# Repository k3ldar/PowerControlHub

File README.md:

# PowerControlHub  
PowerControlHub is an Arduino-based 12V power distribution and control system for marine and off-grid applications. It provides configurable fused relay switching, multi-protocol sensor telemetry, WiFi/BLE/MQTT connectivity, and a companion touchscreen control panel — all managed through a unified serial command protocol and EEPROM-persisted configuration.

> Current firmware version: **1.0.0.0** — see [`FirmwareVersion.h`](PowerControlHub/FirmwareVersion.h).

---

## Table of Contents

- [Overview](#overview)
- [Prototype PCBs](#prototype-pcbs)
- [Key Features](#key-features)
- [Architecture](#architecture)
- [Board Support](#board-support)
- [Installation](#installation)
- [Configuration](#configuration)
- [Usage](#usage)
- [Subsystem Reference](#subsystem-reference)
- [Limitations and Known Issues](#limitations-and-known-issues)
- [Documentation](#documentation)
- [License](#license)

## Overview

PowerControlHub is a single-unit firmware target running on an Arduino Uno R4 WiFi or ESP32 NodeMCU-32. The Nextion touchscreen display is driven directly by the PCH controller over a dedicated hardware serial port (`Serial2` for GPS; display connected via `NextionControl`).

The firmware entry point is `PowerControlHubApp`, which owns all subsystem instances and wires them together at startup. Host and debug communication uses a text-based framed serial protocol:

```
<CMD>:<key>=<value>;<key>=<value>\n
```

Commands are grouped by prefix (`F`, `C`, `R`, `H`, `W`, `S`, `M`, `N`, `E`, `T`) and are available over serial, USB, and — where applicable — the HTTP REST API. See [Docs/Commands.md](Docs/Commands.md) for the full reference.

---

## Prototype PCBs

Prototype PCBs for **PowerControlHub** were supported by [PCBWay](https://www.pcbway.com), enabling rapid iteration from design to real-world testing.

See the [PCB Sponsorship & Manufacturing](Docs/pcbway.md) page for photos, build details, and ongoing testing.

---
## Key Features

### Relay Control
- Up to **8 independently configurable relay channels**, pin-assigned at runtime via configuration.
- **Linked relays** — any relay can be configured to mirror the state of another.
- **Default-on state** — individual relays can be initialised to active at boot.
- **Pulse mode** — relay activates for a configurable duration (seconds) then turns off automatically.
- **Named relays** — short name (5 chars) and long name (20 chars) stored in EEPROM for display use.
- **Action types** — relays can be designated as `Default`, `Horn` (COLREGS sound signal output), or `NightRelay` (automatic day/night switching driven by the LDR sensor).
- **Relay status bitmask** broadcast via `MessageBus` on every state change.

### Sensor Pipeline

All sensors inherit from `BaseSensor` and are registered with `SensorController`. The `RemoteSensor` class provides an extensibility point for sensors on external devices that push readings via serial.

| Sensor | Class | Poll Interval | Notes |
|---|---|---|---|
| **DHT11** | `Dht11SensorHandler` | 2 500 ms | Temperature (°C) and relative humidity (%). Raises `TemperatureSensorFailure` warning on read error; clears automatically on recovery. |
| **Light (LDR)** | `LightSensorHandler` | 30 000 ms | Rolling average over 10 readings. 3-reading debounce before day/night state change. Configurable ADC threshold (default 512). Drives a `NightRelay` automatically. |
| **Water Level** | `WaterSensorHandler` | Configurable | 15-reading rolling average. Active-pin corrosion-reduction control (power applied only during measurement). |
| **GPS** | `GpsSensorHandler` | Continuous | GY-GPS6MV2 (NMEA). Reports latitude, longitude, altitude, speed (km/h), course, cumulative distance. Provides UTC time for automatic RTC synchronisation. Raises `GpsFailure` warning if no valid fix for 30 seconds. |
| **System Diagnostics** | `SystemSensorHandler` | Configurable | Free heap memory, CPU usage percentage, WiFi/BT enabled state, SD log file size (bytes), system uptime (`d HH:MM:SS`), active warning count. |

Sensors expose data over Serial, WiFi REST, BLE, and MQTT. Custom local or remote sensors can be added with minimal boilerplate; see [Docs/Sensors.md](Docs/Sensors.md).

### Connectivity

#### WiFi
- Operates in **Access Point** or **Client** mode, selectable via `C12`.
- Implements **persistent HTTP connections** to reduce TCP handshake overhead on resource-constrained hardware.
- Supports up to **8 concurrent clients** (`MaxConcurrentClients`).
- Automatic reconnection with exponential backoff in Client mode.
- RSSI monitoring — raises `WeakWifiSignal` warning when signal falls below −70 dBm.
- Full REST API across 9 route groups:

| Route | Handler | Purpose |
|---|---|---|
| `/api/relay` | `RelayNetworkHandler` | Relay state read/write |
| `/api/sensor` | `SensorNetworkHandler` | Sensor telemetry |
| `/api/sound` | `SoundNetworkHandler` | COLREGS horn signals |
| `/api/system` | `SystemNetworkHandler` | System status, heartbeat, OTA |
| `/api/config` | `ConfigNetworkHandler` | Configuration read/write |
| `/api/warning` | `WarningNetworkHandler` | Warning bitmask access |
| `/api/timer` | `SchedulerNetworkHandler` | Scheduled event read |
| `/api/externalsensor` | `ExternalSensorNetworkHandler` | Remote sensor config |
| `/` | `WebIndexNetworkHandler` | Index page |

Uses a platform-abstraction interface (`IWifiRadio`) to isolate board-specific WiFi drivers from application logic.

#### Bluetooth BLE
- Available on boards with `BLUETOOTH_SUPPORT` defined.
- Exposes three GATT services via `BluetoothManager`:
  - `BluetoothSystemService` — system diagnostics characteristics.
  - `BluetoothSensorService` — sensor telemetry characteristics with notifications.
  - `BluetoothRelayService` — relay state read and write characteristics.
- Single-client model. Advertising restarts automatically after disconnect.
- No pairing or bonding. Device advertises as **"Power Control Hub"**.
- Uses `IBluetoothRadio` interface — higher-level code operates exclusively through the interface pointer, with runtime null-checks replacing compile-time guards.
- **Arduino Uno R4 WiFi constraint:** WiFi and BLE share the RF path on the ANNA-B112/ESP32-S3 modules; `BLUETOOTH_SUPPORT` and `WIFI_SUPPORT` are mutually exclusive on this board. Enforced by a compile-time `#error`. On ESP32, both can operate simultaneously.

#### MQTT
- Custom **MQTT 3.1.1** client implementation (`MQTTClient`) — no third-party MQTT library dependency.
- **Home Assistant auto-discovery** — all sensors and relays register as HA entities on connect.
- Configurable broker address (64 chars), credentials (32 chars each), device ID, discovery prefix, port (default 1883), and keepalive interval (default 60 s).
- Requires `WIFI_SUPPORT`. Guarded by `#if defined(WIFI_SUPPORT)` in `BoardConfig.h`.

### Warning System

A **32-bit bitmask** tracks up to 32 independent typed conditions within `WarningManager`.

- **Sensor failure aggregation**: any sensor warning (bits 21–31) automatically raises `SensorFailure` (bit 20). `SensorFailure` clears only when all sensor warnings are cleared.
- Warning state changes are broadcast on the `MessageBus` via `WarningChanged`.
- Full warning type reference: [Docs/Warnings.md](Docs/Warnings.md).

### Scheduler

Event-driven relay automation engine with EEPROM-persisted configuration.

- Up to **20 events** (6 on boards with ≤ 1 KB EEPROM) stored in `SchedulerSettings`.
- Each event specifies an independent **trigger**, **condition guard**, and **action**.

| Dimension | Supported Values |
|---|---|
| **Triggers** | `TimeOfDay`, `Sunrise`, `Sunset`, `Interval`, `DayOfWeek`, `Date` |
| **Conditions** | `TimeWindow`, `DayOfWeek`, `IsDark`, `IsDaylight`, `RelayIsOn`, `RelayIsOff` |
| **Actions** | `RelayOn`, `RelayOff`, `RelayToggle`, `RelayPulse`, `AllRelaysOn`, `AllRelaysOff`, `SetPinHigh`, `SetPinLow` |

Sunrise and sunset triggers are computed in real time from GPS coordinates by `SunCalculator`. The `IsDark` / `IsDaylight` conditions fall back to the LDR sensor when GPS is unavailable.

### Message Bus

`MessageBus` provides a **lightweight publish/subscribe event system** for internal component decoupling. No dynamic allocation occurs at publish time — subscriber lists use function-local statics.

Key events: `WarningChanged`, `RelayStatusChanged`, `TemperatureUpdated`, `HumidityUpdated`, `LightSensorUpdated`, `WaterLevelUpdated`, `GpsLocationUpdated`, `GpsAltitudeUpdated`, `GpsSpeedUpdated`, `WifiConnectionStateChanged`, `WifiSignalStrengthChanged`, `SystemMetricsUpdated`. Full reference: [Docs/MessageBus.md](Docs/MessageBus.md).

### Over-the-Air Updates (OTA)

- Available on **ESP32 + `WIFI_SUPPORT` + `OTA_AUTO_UPDATE`** only.
- Polls the GitHub Releases API (`k3ldar/PowerControlHub`) every **24 hours**.
- Downloads asset `PowerControlHub-esp32-v{major}.{minor}.{patch}.{build}.bin` with SHA-256 checksum verification.
- TLS connections use pinned root CA certificates (Sectigo E46 for `api.github.com`; ISRG Root X1 for `assets.githubusercontent.com`).
- **Auto-apply is disabled by default.** Enable via `F12:apply=1` or the `OtaFlagAutoApply` bit in `SystemHeader::reserved[0]`.
- OTA state (`idle`, `checking`, `available`, `downloading`, `rebooting`, `failed`, `uptodate`) is queryable at any time via `F13`.

### Diagnostics and Logging

- **SD card logging** via `SdCardLogger` / `MicroSdDriver`. Configurable SPI pins (`C4`). Raises `SpiPinConfigError`, `SdCardMissing`, `SdCardError`, or `SdCardLowSpace` warnings as appropriate.
- Optional **SD card config loader** (`CARD_CONFIG_LOADER`) — reads `config.txt` at boot to override EEPROM settings without reflashing.
- **DS1302 RTC** (`RtcDS1302Driver`) with configurable pins (`C18`). Automatically synchronised from GPS UTC time on each valid GPS fix.
- **CPU usage monitoring** via `SystemCpuMonitor`. Available over serial, WiFi, and MQTT.
- **Boot counter** and **crash counter** tracked in `SystemHeader` with magic number validation (`0x53464201`).
- **RGB LED warning indicator** (HW479) driven on configurable pins (`C8`).
- **PinGuard** — compile-time GPIO validation layer that rejects flash-reserved, input-only, and strapping pins at the point of assignment, returning `ACK:<cmd>=Invalid pin` before the value reaches EEPROM. Board-specific tables are selected automatically from the IDF toolchain macros — no manual configuration required. See [Docs/PinGuard.md](Docs/PinGuard.md).
- **Crash loop guard** — `crashCounter` in `SystemHeader` is incremented at the start of every boot and only reset after full initialisation succeeds. If the counter reaches `CrashCounterThreshold` (default 3), the firmware resets the config to safe defaults before any hardware initialisation runs, breaking a watchdog reset loop caused by invalid pin configuration.

### Nextion Display

- `NavigationController` manages an ordered list of active pages, rebuilt dynamically when the location type changes — no reboot required.
- Maritime-specific pages (buoys, cardinal markers, flags, VHF radio, COLREGS sound signals) are included in the page list only when `LocationType` is `Power`, `Sail`, `Fishing`, or `Yacht`.
- Pages included: Splash, Home, Relay, Relay Settings, Environment, System, Warning, Settings, About, Buoys, Cardinal Markers, Flags, Moon Phase, Sound (Fog / Maneuvering / Overtaking / Emergency / Other / Signals), VHF (Channels / Distress / Radio).

### Security

- **API key and HMAC key** fields (32 chars each) are reserved in the `Config` struct for future HTTP authentication.

---

## Architecture

### Repository Structure

```
PowerControlHub/    Firmware source (relays, sensors, WiFi, BLE, MQTT, OTA, SD, Nextion display)
Docs/            Reference documentation
TestData/        Serial command test scripts
```

### Subsystem Dependency Graph

```
PowerControlHubApp
├── MessageBus                  Pub/sub event bus (no dynamic allocation)
├── RelayController             Relay switching, linking, pulse, action types
├── SoundController             COLREGS signal sequencer -> horn relay
├── SensorController            Sensor pipeline (local + remote)
│   ├── Dht11SensorHandler
│   ├── LightSensorHandler
│   ├── WaterSensorHandler
│   ├── GpsSensorHandler
│   ├── SystemSensorHandler
│   └── RemoteSensor (xN)
├── ConfigController            EEPROM config lifecycle
├── WarningManager              32-bit bitmask, sensor failure aggregation
├── ScheduleController          Event engine: trigger -> condition -> action
├── WifiController              WiFi lifecycle, HTTP REST API
│   └── WifiServer              Connection state machine, request routing
├── BluetoothController         BLE lifecycle (BLUETOOTH_SUPPORT)
│   └── BluetoothManager
│       ├── BluetoothSystemService
│       ├── BluetoothSensorService
│       └── BluetoothRelayService
├── MQTTController              MQTT 3.1.1 client, HA auto-discovery (MQTT_SUPPORT)
├── SdCardLogger                SD card log writer (SD_CARD_SUPPORT)
├── RtcDS1302Driver             DS1302 real-time clock
├── OtaManager                  GitHub OTA (OTA_AUTO_UPDATE + ESP32 + WIFI_SUPPORT)
├── BroadcastManager            Centralised serial broadcast to computer/debug port
├── NavigationController        Nextion page navigation (NEXTION_DISPLAY_DEVICE)
└── SerialCommandManager        Framed serial command dispatch (USB/debug)
```

### Interface Abstraction Pattern

WiFi and Bluetooth subsystems are each accessed through a platform-agnostic interface (`IWifiRadio`, `IBluetoothRadio`). Board-specific drivers (`R4WifiRadio`, `Esp32WifiRadio`, `BluetoothController`) are constructed only inside `PowerControlHubApp` under the appropriate `#if defined(...)` guard. All higher-level code operates through interface pointers with runtime null-checks, minimising preprocessor usage and enabling straightforward test doubles.

### Configuration Persistence

The `Config` struct is a versioned, packed POD serialised to EEPROM. The current layout version is **6** (`ConfigVersion6`). The `SystemHeader` (32 bytes) precedes the config payload and contains a magic number (`0x53464201`), boot count, crash counter, reset reason, OTA flags, and a 16-bit checksum. A config version mismatch triggers migration logic in `ConfigManager` and raises `DefaultConfigurationFuseBox`.

---

## Board Support

| Board | WiFi | BLE | MQTT | OTA | Notes |
|---|---|---|---|---|---|
| **Arduino Uno R4 WiFi** | Yes | Yes | Yes | No | WiFi and BLE are mutually exclusive (shared RF path) |
| **Arduino Uno R4 Minima** | No | No | No | No | Serial and sensor support only |
| **ESP32 NodeMCU-32** | Yes | Yes | Yes | Yes | Full feature support; WiFi and BLE simultaneous |

Board selection is controlled by a single `#define` in `Local.h` using the trailing-underscore convention. `BoardConfig.h` derives all capability flags, EEPROM limits, and enforces incompatible feature combinations at compile time.

---

## Installation

### Prerequisites

| Requirement | Details |
|---|---|
| **Arduino IDE** | 1.8.19 or Arduino IDE 2.x |
| **Git for Windows** | Standard installation |
| **Windows 10 / 11** | No special configuration required |

### Required Libraries (Arduino Library Manager)

| Library | Source |
|---|---|
| `SerialCommandManager` | Si Carter |
| `DHT sensor library` | Adafruit |
| `QMC5883LCompass` | Arduino Library Manager |
| `NextionControl` | Custom — copy `NextionControl/` folder to Arduino `libraries/` directory |

### Steps

1. Clone the repository:

   ```
   git clone https://github.com/k3ldar/PowerControlHub
   ```

2. Install all required libraries via the Arduino IDE Library Manager, and copy `NextionControl` manually.

3. Open `k3ldar/PowerControlHub.ino` in the Arduino IDE.

4. Edit `Local.h` to activate the correct board and feature flags (see [Configuration](#configuration)).

5. Select the target board and COM port, then upload.

Full setup walkthrough: [Docs/SETUP.md](Docs/SETUP.md).

---

## Configuration

All hardware-specific configuration is isolated in a single file: `PowerControlHub/Local.h`. No other file requires modification for a standard hardware setup.

### Board Selection

Exactly one board define must be active. Remove the trailing underscore to activate:

```cpp
#define ARDUINO_UNO_R4       // Arduino Uno R4 WiFi
#define ARDUINO_R4_MINIMA_   // Arduino Uno R4 Minima (inactive)
#define ESP32_NODE_32_       // ESP32 NodeMCU-32 (inactive)
```

### Feature Flags

| Define | Default | Approx. Flash | Description |
|---|---|---|---|
| `FUSE_BOX_CONTROLLER` | Active | — | Enables the full SFB subsystem stack |
| `WIFI_SUPPORT` | Active | — | WiFi controller and HTTP REST API |
| `MQTT_SUPPORT` | Active | ~40 KB | MQTT client and HA auto-discovery (requires `WIFI_SUPPORT`) |
| `BLUETOOTH_SUPPORT` | Inactive | ~144 KB | BLE services (mutually exclusive with WiFi on Uno R4) |
| `SD_CARD_SUPPORT` | Active | ~32 KB | SD card logger and SPI driver |
| `NEXTION_DISPLAY_DEVICE` | Active | ~52 KB | Nextion display page system |
| `OTA_AUTO_UPDATE` | Active | ~165 KB | GitHub OTA (ESP32 + WiFi only) |
| `LED_MANAGER` | Inactive | — | Arduino R4 WiFi LED matrix (experimental) |
| `CARD_CONFIG_LOADER` | Inactive | — | Load config overrides from SD `config.txt` at boot |

### Relay Count

```cpp
constexpr uint8_t ConfigRelayCount = 8;  // number of relay channels
```

Pins are assigned at runtime via the `R11` serial command and persisted to EEPROM. `0xFF` marks a pin as unassigned.

Full configuration reference: [Docs/Local.md](Docs/Local.md).

---

## Usage

### Serial / USB Commands (Quick Reference)

Commands follow the frame format: `<CMD>:<key>=<value>;<key>=<value>\n`

```
# Save config to EEPROM
C0

# Enable WiFi in client mode, set SSID and password
C11:v=1
C12:v=1
C13:YourSSID
C14:YourPassword
C0

# Switch relay 0 on / off
R3:i=0;v=1
R3:i=0;v=0

# Query all relay states
R2

# Read temperature and humidity
S0
S1

# Enable MQTT and set broker
M0:v=1
M1:192.168.1.100
C0

# Enable Home Assistant auto-discovery
M6:v=1

# Query OTA status (ESP32 only)
F13

# Check for firmware update
F12

# Apply firmware update immediately
F12:apply=1
```

Full command reference (all groups, all parameters): [Docs/Commands.md](Docs/Commands.md).

### HTTP REST API (WiFi)

```
# Relay control
POST /api/relay/R3?i=0&v=1

# Sensor data
GET /api/sensor/S0

# System status
GET /api/system/F2

# OTA status
GET /api/system/F13
```

---

## Subsystem Reference

| Document | Contents |
|---|---|
| [Docs/Commands.md](Docs/Commands.md) | Full serial and REST command reference (all groups F, C, R, H, W, S, M, N, E, T) |
| [Docs/Local.md](Docs/Local.md) | `Local.h` configuration reference: board selection, feature flags, pin layout |
| [Docs/PinGuard.md](Docs/PinGuard.md) | GPIO validation: board pin tables, blocked pin tiers, crash loop guard |
| [Docs/Sensors.md](Docs/Sensors.md) | Sensor classes, poll intervals, MQTT channels, warning behaviour, extensibility guide |
| [Docs/Warnings.md](Docs/Warnings.md) | 32-bit warning type reference, `WarningManager` API, propagation model |
| [Docs/Wifi.md](Docs/Wifi.md) | WiFi architecture: connection state machine, persistent connection model, handler pattern |
| [Docs/BluetoothBle.md](Docs/BluetoothBle.md) | BLE service/characteristic reference, connection model, adding new services |
| [Docs/ScheduleEvents.md](Docs/ScheduleEvents.md) | Scheduler data structures, trigger/condition/action types, EEPROM layout |
| [Docs/MessageBus.md](Docs/MessageBus.md) | Event reference, publish/subscribe API |
| [Docs/SETUP.md](Docs/SETUP.md) | Prerequisites, library installation, build instructions |
| [Docs/BOM.md](Docs/BOM.md) | Bill of materials: hardware, fasteners, connectors, 3D-printed parts |

---

## Limitations and Known Issues

- **Arduino Uno R4 WiFi**: WiFi and BLE cannot operate simultaneously due to the shared RF hardware path. This is enforced at compile time.
- **Arduino Uno R4 Minima**: No radio support. Serial, sensors, and Nextion display only.
- **OTA updates**: Restricted to ESP32 targets with WiFi in client mode and `OTA_AUTO_UPDATE` defined. Not available on Arduino Uno R4.
- **Scheduler capacity**: Limited to 6 events on boards with 1 KB or less of EEPROM.
- **LED matrix manager** (`LED_MANAGER`): Experimental on Arduino R4 WiFi; not recommended for production use.
- **SD card support**: Marked experimental in `Local.h`. SPI pin configuration must be correct or `SpiPinConfigError` is raised.
- **Single BLE client**: Only one BLE central can be connected at a time. No pairing or bonding is implemented.

---

## Documentation

| Getting Started | Configuration | Connectivity |
|:---|:---|:---|
| [Setup Guide](Docs/SETUP.md) | [Local.h Reference](Docs/Local.md) | [WiFi Architecture](Docs/Wifi.md) |
| [Bill of Materials](Docs/BOM.md) | [Scheduled Events](Docs/ScheduleEvents.md) | [Bluetooth BLE](Docs/BluetoothBle.md) |
| [Sensor Reference](Docs/Sensors.md) | [Warning System](Docs/Warnings.md) | [Message Bus](Docs/MessageBus.md) |
| [Command Reference](Docs/Commands.md) | [PinGuard & Crash Loop](Docs/PinGuard.md) | |

---

## License

PowerControlHub is released under the **GNU General Public License v3.0**.  
See [LICENSE](LICENSE) for the full licence text.

Copyright &copy; 2025 Simon Carter (`s1cart3r@gmail.com`)

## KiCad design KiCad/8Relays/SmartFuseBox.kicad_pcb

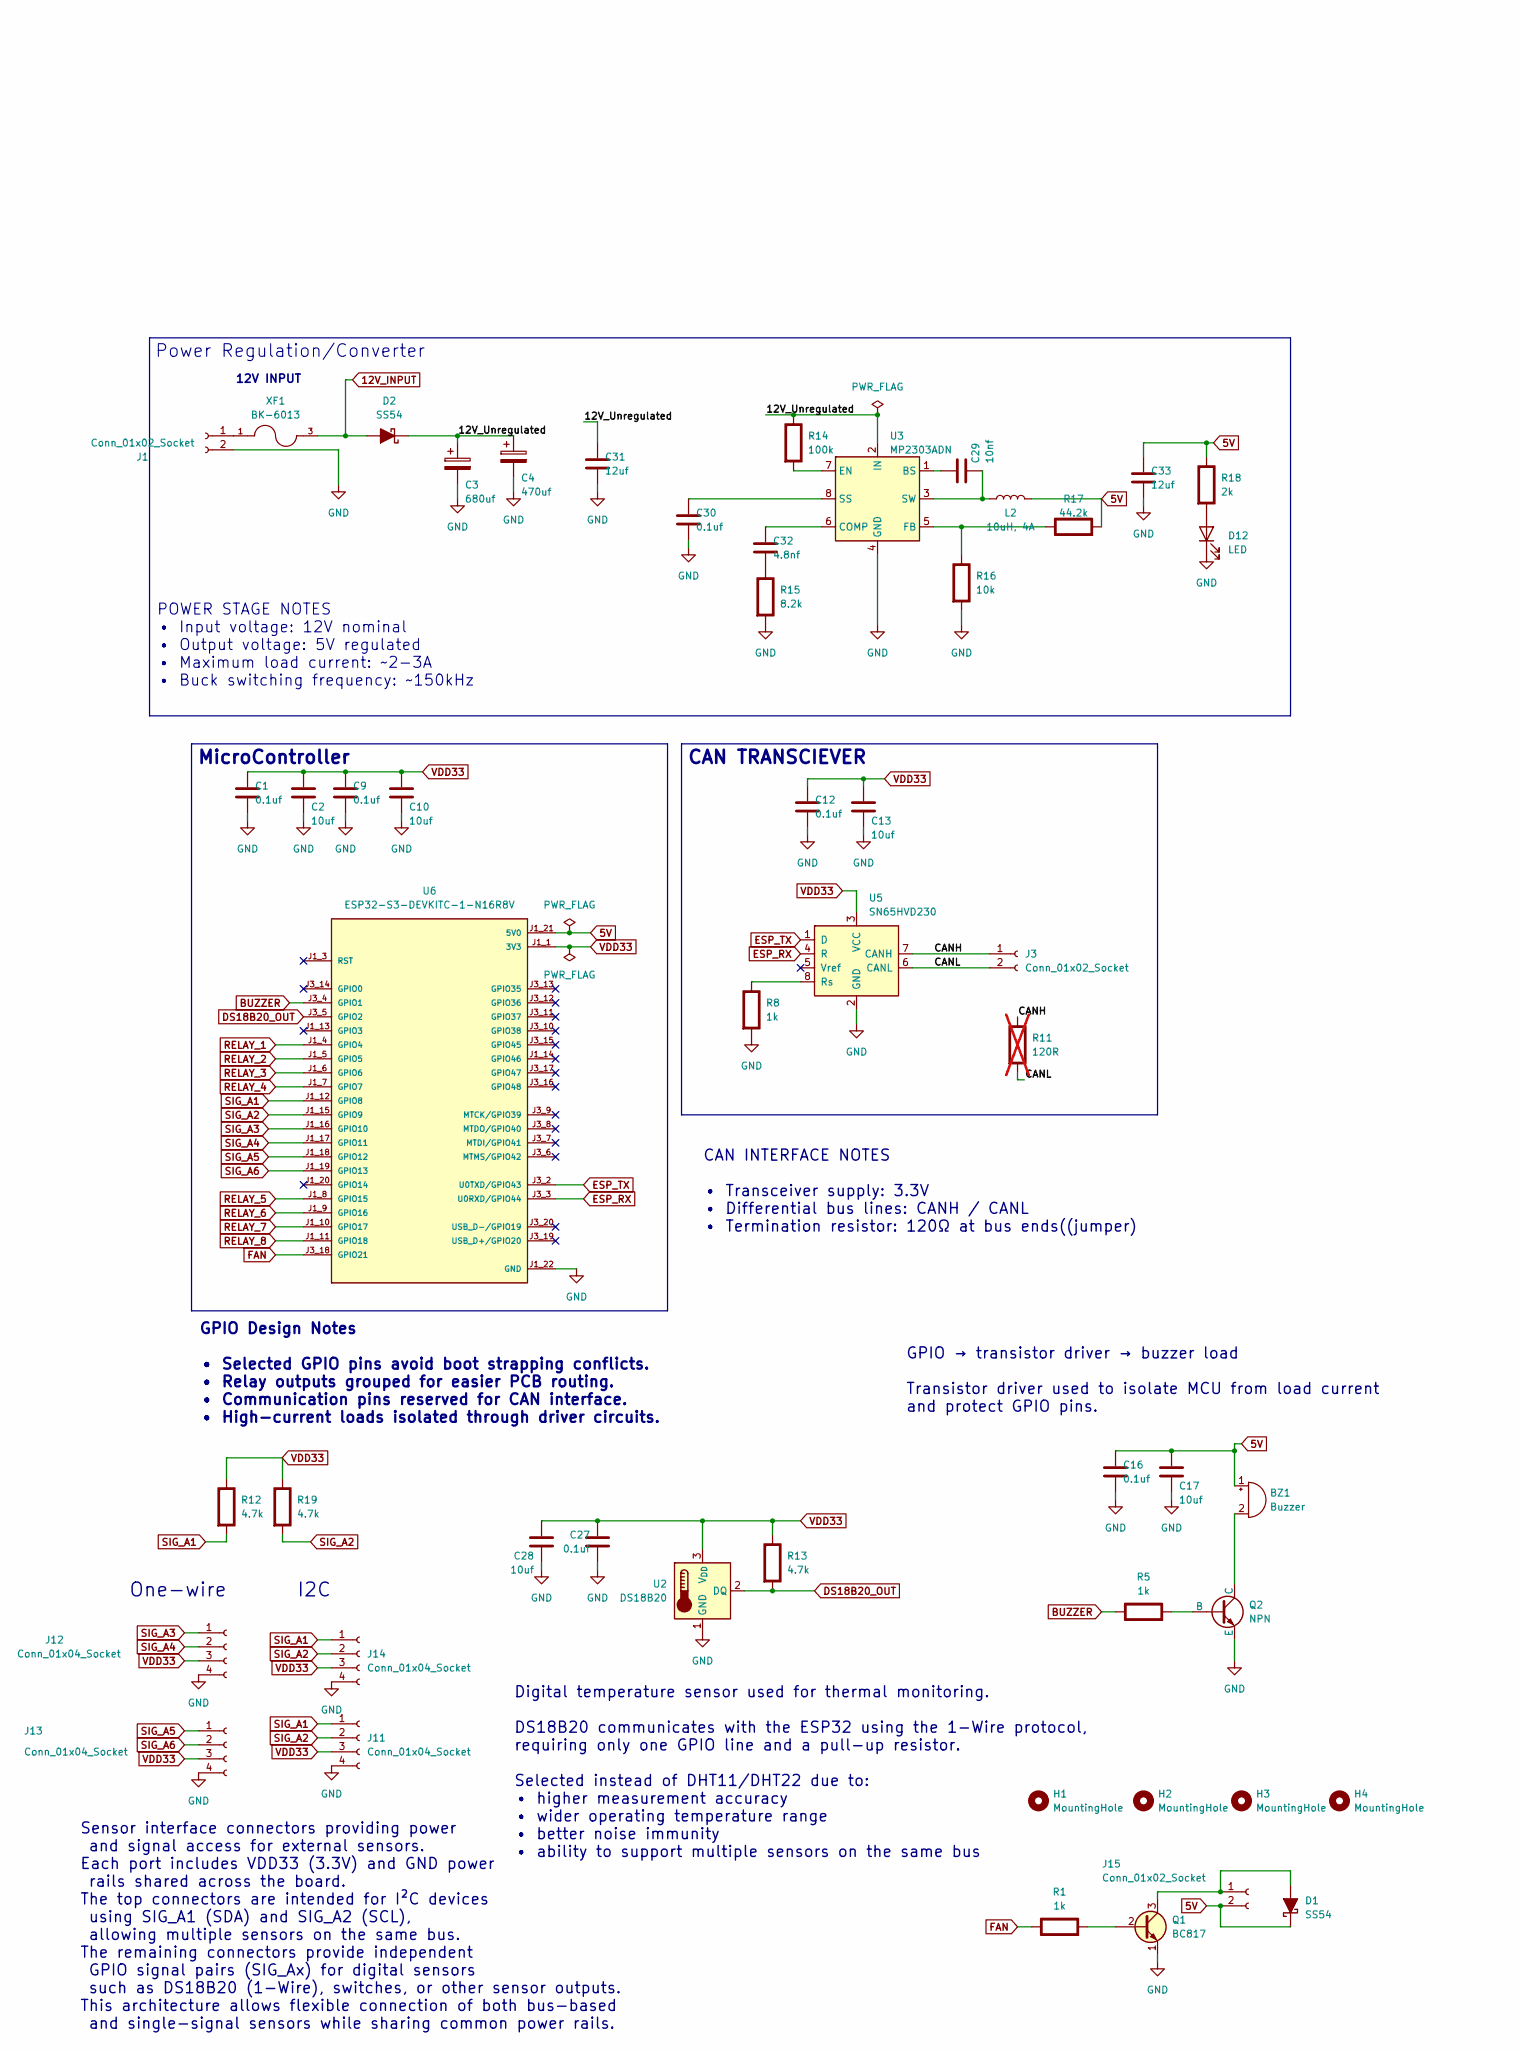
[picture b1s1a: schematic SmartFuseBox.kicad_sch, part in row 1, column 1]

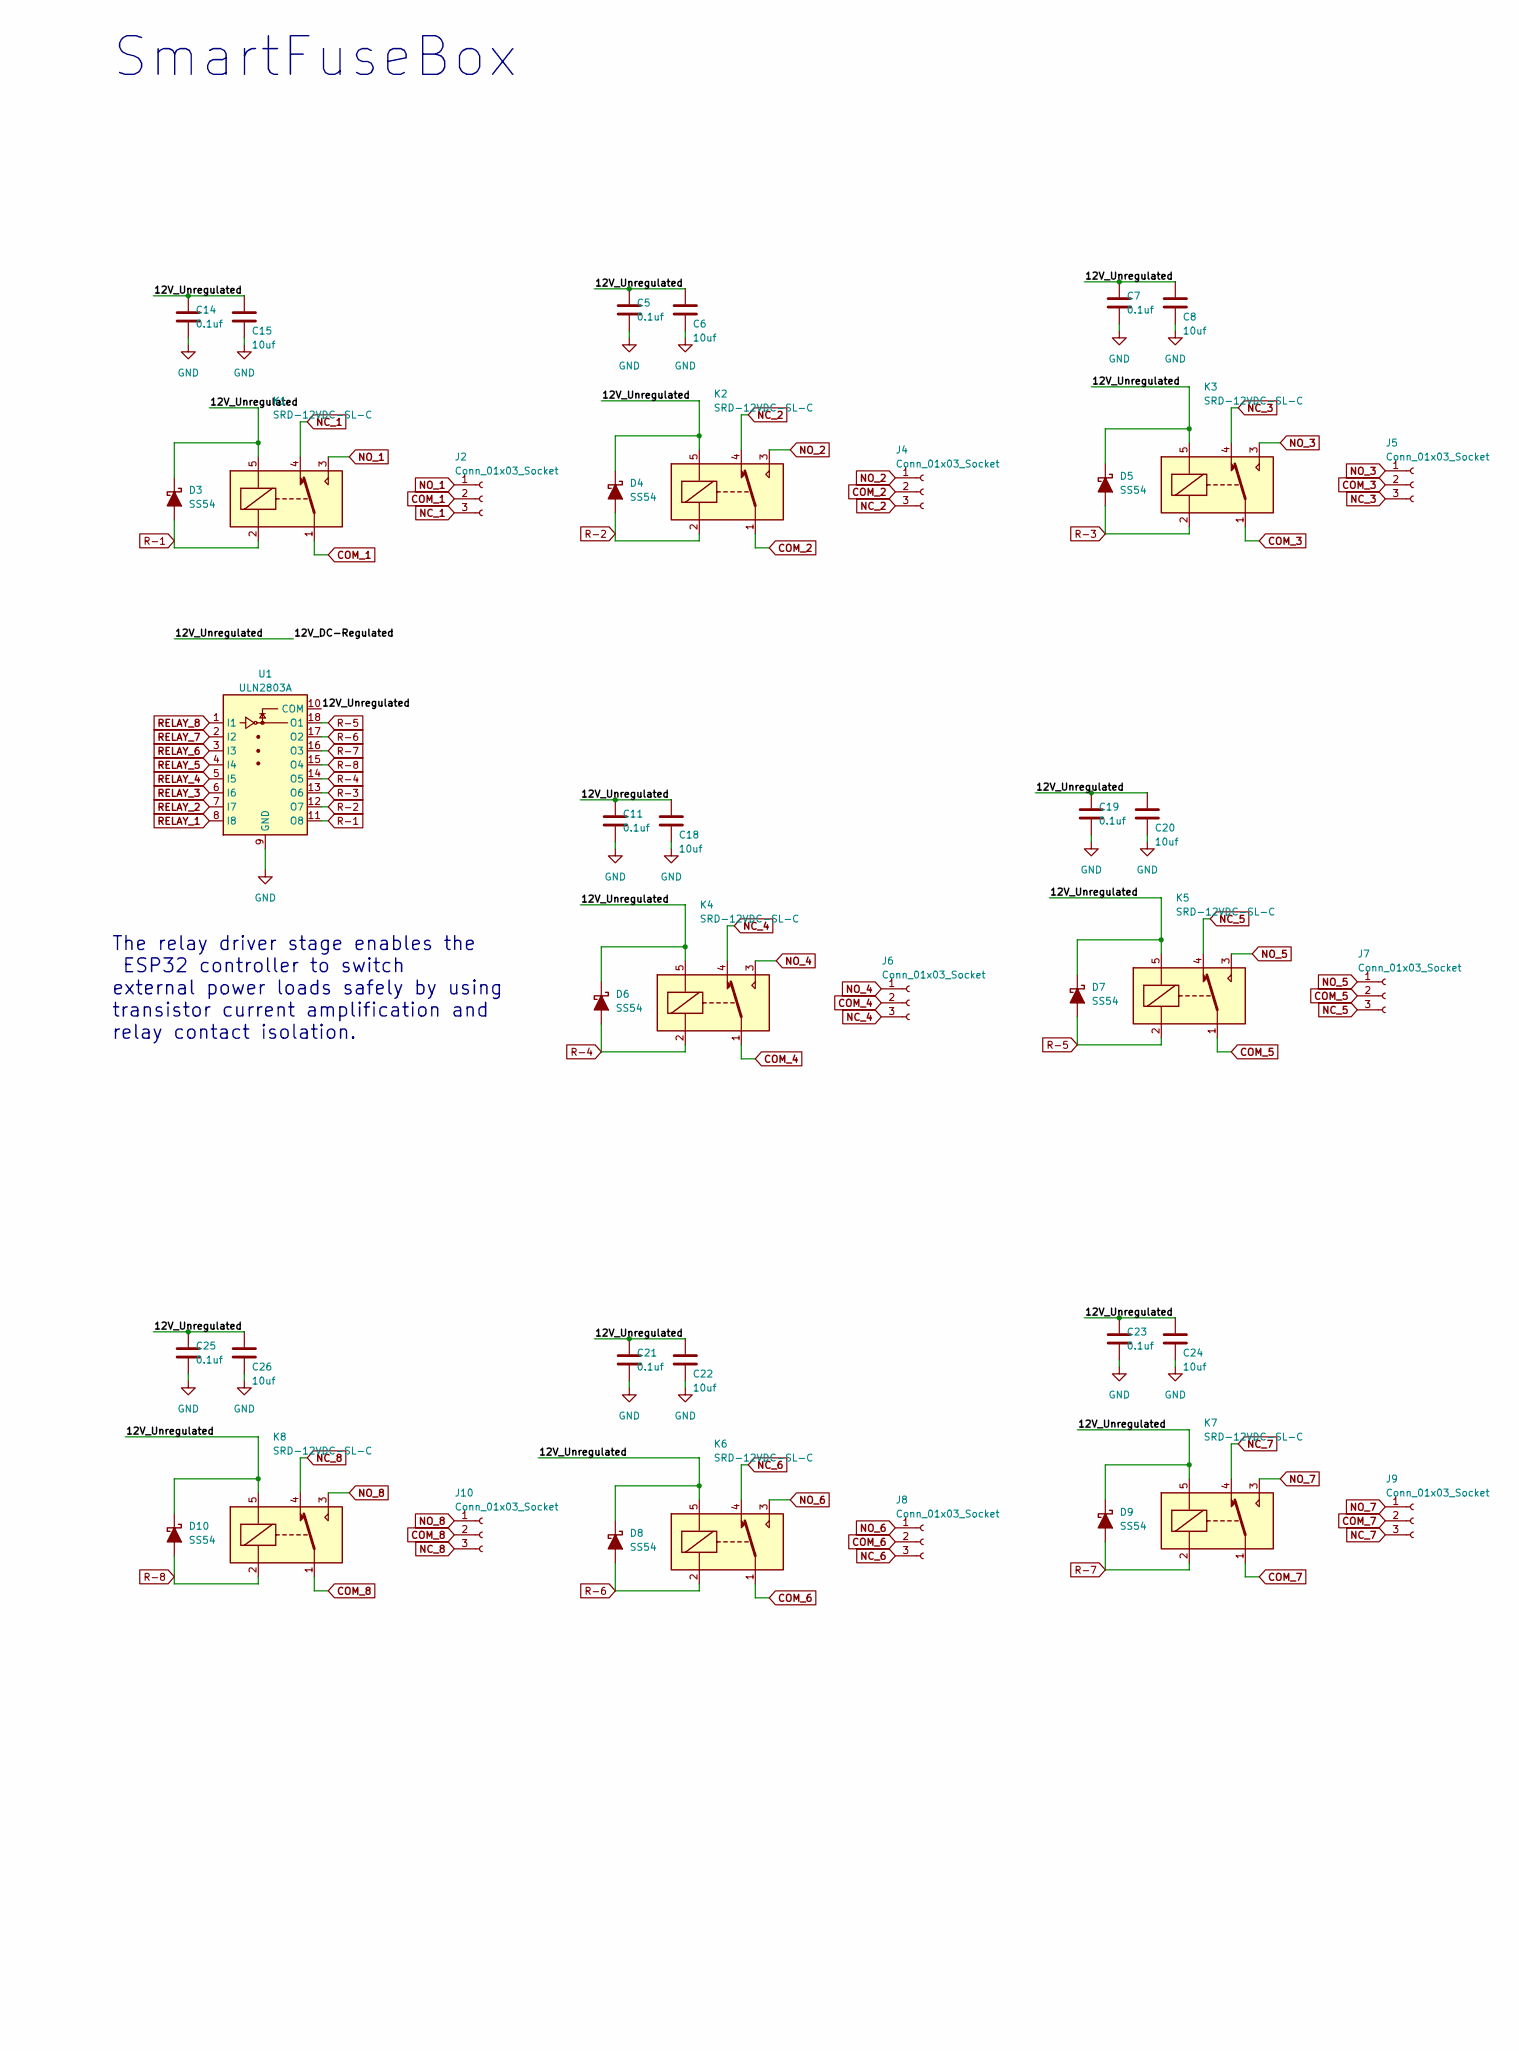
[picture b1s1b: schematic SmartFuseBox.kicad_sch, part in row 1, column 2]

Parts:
BZ1: Buzzer; Buzzer_12x9.5RM7.6
C1, C5, C7, C9, C11, C12, C14, C16, C19, C21, C23, C25, C27, C30: 0.1uf; C_0805_2012Metric_Pad1.18x1.45mm_HandSolder
C2, C6, C8, C10, C13, C15, C17, C18, C20, C22, C24, C26, C28: 10uf; C_0805_2012Metric_Pad1.18x1.45mm_HandSolder
C3: 680uf; CP_Elec_6.3x7.7
C4: 470uf; CP_Elec_10x10.5
C29: 10nf; C_0805_2012Metric_Pad1.18x1.45mm_HandSolder
C31, C33: 12uf; C_0805_2012Metric_Pad1.18x1.45mm_HandSolder
C32: 4.8nf; C_0805_2012Metric_Pad1.18x1.45mm_HandSolder
D1, D2, D3, D4, D5, D6, D7, D8, D9, D10: SS54; D_SMA
D12: LED; LED_0805_2012Metric_Pad1.15x1.40mm_HandSolder
H1, H2, H3, H4: MountingHole; MountingHole_3.2mm_M3
J1, J3: Conn_01x02_Socket; TerminalBlock_MaiXu_MX126-5.0-02P_1x02_P5.00mm
J2, J4, J5, J6, J7, J8, J9, J10: Conn_01x03_Socket; TerminalBlock_MaiXu_MX126-5.0-03P_1x03_P5.00mm
J11, J12, J13, J14: Conn_01x04_Socket; JST_PH_S4B-PH-K_1x04_P2.00mm_Horizontal
J15: Conn_01x02_Socket; JST_XH_S2B-XH-A-1_1x02_P2.50mm_Horizontal
K1, K2, K3, K4, K5, K6, K7, K8: SRD-12VDC-SL-C; Relay_SPDT_SANYOU_SRD_Series_Form_C
L2: 10uH, 4A; L_SOREDE_SNR.1050_10x10x5mm
Q1: BC817; SOT-23
Q2: NPN; SOT23-3_PO123
R1, R5, R8: 1k; R_0805_2012Metric_Pad1.20x1.40mm_HandSolder; Rating W
R11: 120R; R_0805_2012Metric_Pad1.20x1.40mm_HandSolder; Rating W; not fitted
R12, R13, R19: 4.7k; R_0805_2012Metric_Pad1.20x1.40mm_HandSolder; Rating W
R14: 100k; R_0805_2012Metric_Pad1.20x1.40mm_HandSolder; Rating W
R15: 8.2k; R_0805_2012Metric_Pad1.20x1.40mm_HandSolder; Rating W
R16: 10k; R_0805_2012Metric_Pad1.20x1.40mm_HandSolder; Rating W
R17: 44.2k; R_0805_2012Metric_Pad1.20x1.40mm_HandSolder; Rating W
R18: 2k; R_0805_2012Metric_Pad1.20x1.40mm_HandSolder; Rating W
U1: ULN2803A; SOIC-18W_7.5x11.6mm_P1.27mm
U2: DS18B20; TO-92_Inline
U3: MP2303ADN; SOIC-8-1EP_3.9x4.9mm_P1.27mm_EP2.62x3.51mm
U5: SN65HVD230; SOIC-8_3.9x4.9mm_P1.27mm
U6: ESP32-S3-DEVKITC-1-N16R8V; XCVR_ESP32-S3-DEVKITC-1-N16R8V; PARTREV 1.1
XF1: BK-6013; FUSE_BK-6013; PARTREV 02/07/14

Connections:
5V: BZ1.1 (+), C16.1, C17.1, C33.1, D1.1 (K), J15.2, L2.2, R17.2 (-), R18.1 (+), U6.J1_21 (5V0)
12V_INPUT: D2.2 (A), XF1.3, XF1.4
/12V_DC-Regulated: C3.1, C4.1, C5.1, C6.1, C7.1, C8.1, C11.1, C14.1, C15.1, C18.1, C19.1, C20.1, C21.1, C22.1, C23.1, C24.1, C25.1, C26.1, C31.1, D2.1 (K), D3.1 (K), D4.1 (K), D5.1 (K), D6.1 (K), D7.1 (K), D8.1 (K), D9.1 (K), D10.1 (K), K1.5, K2.5, K3.5, K4.5, K5.5, K6.5, K7.5, K8.5, R14.1 (+), U1.10 (COM), U3.2 (IN)
/CANH: J3.1, R11.1 (+), U5.7 (CANH)
/CANL: J3.2, R11.2 (-), U5.6 (CANL)
BUZZER: R5.1 (+), U6.J3_4 (GPIO1)
COM_1: J2.2, K1.1
COM_2: J4.2, K2.1
COM_3: J5.2, K3.1
COM_4: J6.2, K4.1
COM_5: J7.2, K5.1
COM_6: J8.2, K6.1
COM_7: J9.2, K7.1
COM_8: J10.2, K8.1
DS18B20_OUT: R13.2 (-), U2.2 (DQ), U6.J3_5 (GPIO2)
ESP_RX: U5.4 (R), U6.J3_3 (U0RXD/GPIO44)
ESP_TX: U5.1 (D), U6.J3_2 (U0TXD/GPIO43)
FAN: R1.1 (+), U6.J3_18 (GPIO21)
GND: C1.2, C2.2, C3.2, C4.2, C5.2, C6.2, C7.2, C8.2, C9.2, C10.2, C11.2, C12.2, C13.2, C14.2, C15.2, C16.2, C17.2, C18.2, C19.2, C20.2, C21.2, C22.2, C23.2, C24.2, C25.2, C26.2, C27.2, C28.2, C30.2, C31.2, C33.2, D12.1 (K), J1.2, J11.4, J12.4, J13.4, J14.4, Q1.1 (E), Q2.3 (E), R8.2 (-), R15.2 (-), R16.2 (-), U1.9 (GND), U2.1 (GND), U3.4 (GND), U5.2 (GND), U6.J1_22 (GND), U6.J3_1 (GND), U6.J3_21 (GND), U6.J3_22 (GND)
NC_1: J2.3, K1.4
NC_2: J4.3, K2.4
NC_3: J5.3, K3.4
NC_4: J6.3, K4.4
NC_5: J7.3, K5.4
NC_6: J8.3, K6.4
NC_7: J9.3, K7.4
NC_8: J10.3, K8.4
NO_1: J2.1, K1.3
NO_2: J4.1, K2.3
NO_3: J5.1, K3.3
NO_4: J6.1, K4.3
NO_5: J7.1, K5.3
NO_6: J8.1, K6.3
NO_7: J9.1, K7.3
NO_8: J10.1, K8.3
unnamed: BZ1.2 (-), Q2.1 (C)
unnamed: D1.2 (A), J15.1, Q1.3 (C)
unnamed: D12.2 (A), R18.2 (-)
unnamed: J1.1, XF1.1, XF1.2
unnamed: Q1.2 (B), R1.2 (-)
unnamed: Q2.2 (B), R5.2 (-)
unnamed: R8.1 (+), U5.8 (Rs)
unnamed: R14.2 (-), U3.7 (EN)
unnamed: C32.2, R15.1 (+)
unnamed: R16.1 (+), R17.1 (+), U3.5 (FB)
unnamed: C29.1, U3.1 (BS)
unnamed: C32.1, U3.6 (COMP)
unnamed: C30.1, U3.8 (SS)
unnamed: C29.2, L2.1, U3.3 (SW)
R-1: D3.2 (A), K1.2, U1.11 (O8)
R-2: D4.2 (A), K2.2, U1.12 (O7)
R-3: D5.2 (A), K3.2, U1.13 (O6)
R-4: D6.2 (A), K4.2, U1.14 (O5)
R-5: D7.2 (A), K5.2, U1.18 (O1)
R-6: D8.2 (A), K6.2, U1.17 (O2)
R-7: D9.2 (A), K7.2, U1.16 (O3)
R-8: D10.2 (A), K8.2, U1.15 (O4)
RELAY_1: U1.8 (I8), U6.J1_4 (GPIO4)
RELAY_2: U1.7 (I7), U6.J1_5 (GPIO5)
RELAY_3: U1.6 (I6), U6.J1_6 (GPIO6)
RELAY_4: U1.5 (I5), U6.J1_7 (GPIO7)
RELAY_5: U1.4 (I4), U6.J1_8 (GPIO15)
RELAY_6: U1.3 (I3), U6.J1_9 (GPIO16)
RELAY_7: U1.2 (I2), U6.J1_10 (GPIO17)
RELAY_8: U1.1 (I1), U6.J1_11 (GPIO18)
SIG_A1: J11.1, J14.1, R12.2 (-), U6.J1_12 (GPIO8)
SIG_A2: J11.2, J14.2, R19.2 (-), U6.J1_15 (GPIO9)
SIG_A3: J12.1, U6.J1_16 (GPIO10)
SIG_A4: J12.2, U6.J1_17 (GPIO11)
SIG_A5: J13.1, U6.J1_18 (GPIO12)
SIG_A6: J13.2, U6.J1_19 (GPIO13)
VDD33: C1.1, C2.1, C9.1, C10.1, C12.1, C13.1, C27.1, C28.1, J11.3, J12.3, J13.3, J14.3, R12.1 (+), R13.1 (+), R19.1 (+), U2.3 (V_{DD}), U5.3 (VCC), U6.J1_1 (3V3), U6.J1_2 (3V3)

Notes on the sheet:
Sensor interface connectors providing power and signal access for external sensors. Each port includes VDD33 (3.3V) and GND power rails shared across the board. The top connectors are intended for I²C devices using SIG_A1 (SDA) and SIG_A2 (SCL), allowing multiple sensors on the same bus. The remain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
The relay driver stage enables the ESP32 controller to switch external power loads safely by using transistor current amplification and relay contact isolation.
GPIO Design Notes • Selected GPIO pins avoid boot strapping conflicts. • Relay outputs grouped for easier PCB routing. • Communication pins reserved for CAN interface. • High-current loads isolated through driver circuits.
I2C
CAN INTERFACE NOTES • Transceiver supply: 3.3V • Differential bus lines: CANH / CANL • Termination resistor: 120Ω at bus ends((jumper)
${TITLE}
One-wire
12V INPUT
GPIO → transistor driver → buzzer load Transistor driver used to isolate MCU from load current and protect GPIO pins.
Digital temperature sensor used for thermal monitoring. DS18B20 communicates with the ESP32 using the 1-Wire protocol, requiring only one GPIO line and a pull-up resistor. Selected instead of DHT11/DHT22 due to: • higher measurement accuracy • wider operating temperature range • better noise immuni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
POWER STAGE NOTES • Input voltage: 12V nominal • Output voltage: 5V regulated • Maximum load current: ~2-3A • Buck switching frequency: ~150kHz
Power Regulation/Converter
MicroController
CAN TRANSCIEVER

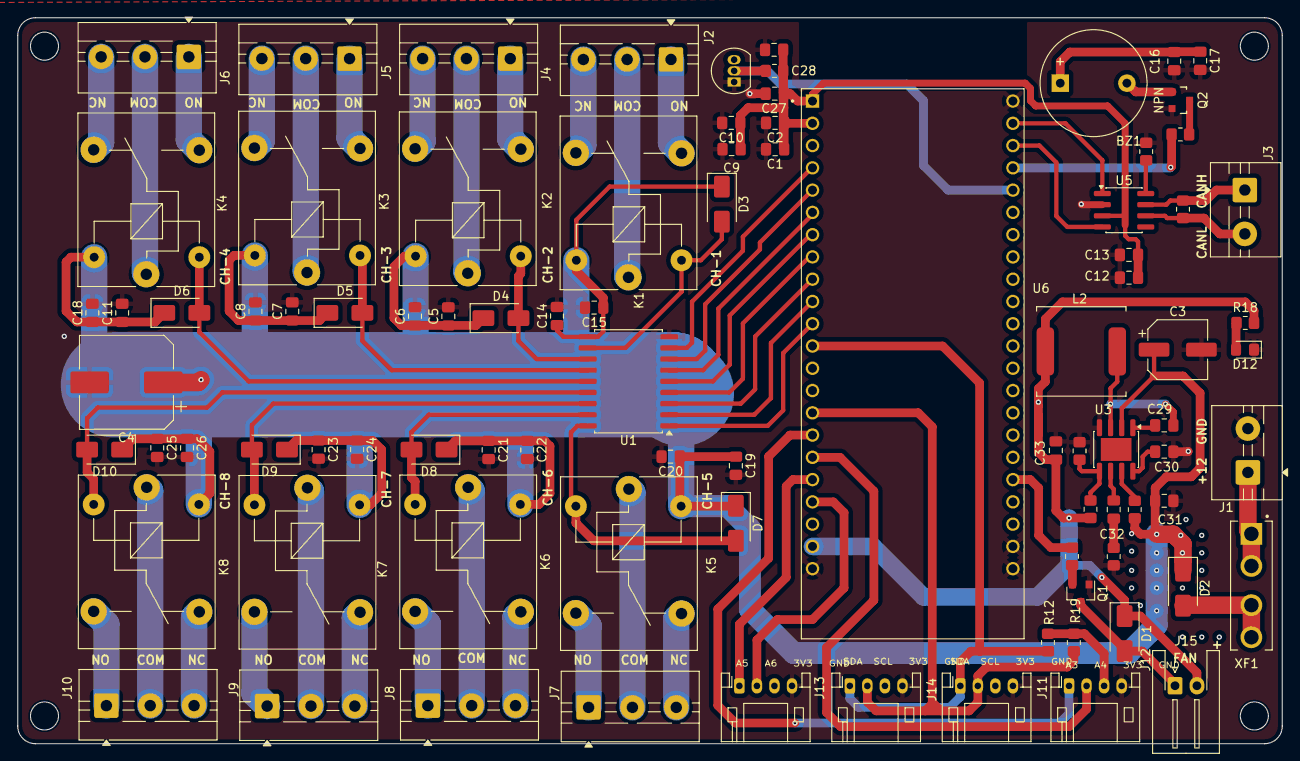
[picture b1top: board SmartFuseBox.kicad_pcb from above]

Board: 4 copper layers, 144.2 x 82.8 mm, 93 parts (0 on the bottom side), 72 nets.

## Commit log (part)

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2025-11-16 Auto name relay for sound commands Include BroadcastManager for multi serial comms
2025-11-16 Initial plan
2025-11-17 Sensor management part 1
2025-11-18 Send warning to control panel
2025-11-20 Initial sharing of code between projects using symbolic links
2025-11-20 Feature/shared code (#36)
    * Initial sharing of code between projects using symbolic links
    * Add board used in local
2025-11-20 Add documentation and error handling to UpdateSymLinks.bat
2025-11-20 Add fixes for sym link files along with documentation
2025-11-20 Add fixes for sym link files along with documentation (#42)
2025-11-21 Clean up SymLink creation and remove duplicate batch code
2025-11-21 Rename StaticElectrics to SmartFuseBox
2025-11-21 Rename StaticElectrics to SmartFuseBox (#43)
2025-11-22 Finalise shared code between projects
2025-11-23 Update warning page, extend for default configuration both sides.
    Fix memory issue on UnoR4
    Cpu Monitoring and new monitor page on nextion
2025-11-24 Update warning page, extend for default configuration both sides. (#45)
    Fix memory issue on UnoR4
    Cpu Monitoring and new monitor page on nextion
2025-11-25 Update global variables which are used within Nextion
2025-11-25 Update global variables which are used within Nextion (#46)
2025-11-25 Fix all global variable names for smoother display
2025-11-25 Implement about page
2025-11-27 Initial bt offering, still has issues before pushing
2025-11-28 Finished bluetooth integration
2025-11-28 add relay service
2025-11-28 Feature/bluetooth (#49)
    * Finished bluetooth integration
2025-11-29 Introduce standard logging
2025-11-29 Fix issue with BroadcastManager and add queue to shared
2025-11-30 Initial non blocking wifi server
2025-11-30 Implement with wifi controller
2025-12-01 Integrate wifi into smart fuse box, only has relay at present, the remainder will form part of other PRs
2025-12-01 Feature/wifi (#54)
    * Initial non blocking wifi server
    * Implement with wifi controller
    * Pre full integration test
    * Integrate wifi into smart fuse box, only has relay at present, the remainder will form part of other PRs
2025-12-01 rename sound manager to sound controller as part of middleware
2025-12-02 Complete sound network handler, refactored existing handler in the process
2025-12-02 Validate wifi strength
2025-12-02 Feature/wifi sound command handler (#67)
    * rename sound manager to sound controller as part of middleware
    * Complete sound network handler, refactored existing handler in the process
    * Complete sound network handler, refactored existing handler in the process
    * Complete sound network handler, refactored existing handler in the process
    * Updates from code review
    * Validate wifi strength
2025-12-03 Warning network handler
    prevent auto reconnect when RSSI is low
2025-12-06 Initial working version
2025-12-06 Partially complete
2025-12-08 SystemNetworkHandler (#77)
2025-12-13 Initial conversion BoatControlPanel compiles
2025-12-13 Convert string from DateTimeManager to char*
2025-12-13 convert string to char* in network base
2025-12-13 Convert handles
2025-12-14 Finished refactor
2025-12-16 Bug fixes and add Cardianl markers page
2025-12-16 Bug fixes and add Cardianl markers page (#86)
2025-12-17 Add buoys page and fix code getting PROGMEM
2025-12-17 Add buoys page and fix code getting PROGMEM (#87)
2025-12-20 Convert to use ConfigController middleware
2025-12-21 set auto on relays, update json being sent for config, introduce LedManager
2025-12-21 Feature/always on relays (#89)
    * Convert to use ConfigController middleware
    * ConfigCommandHandler
    * set auto on relays, update json being sent for config, introduce LedManager
    * Integrate LedManager
    * Finalize initial on relays
2025-12-23 Introduce MessageBus
2025-12-24 Further MessageBus integration
2025-12-25 Compiler flag for LED matrix on R4
2025-12-25 Compiler flag for LED matrix on R4 (#92)
2026-01-10 Move Gps sensor to boat controller
2026-01-10 Working - ish
2026-01-11 Final fix of GPS integration
2026-01-11 Sensor Controller
2026-01-11 sensor command handler update
2026-01-11 Fix speed sensor handling
2026-01-11 Blinking issue with loss of link and using last values
2026-01-25 Configure Config settings from nextion device (#97)
2026-01-27 Environment page (#100)
2026-01-28 Integrate LED light into control panel
2026-01-28 Integrate LED light into control panel (#101)
2026-02-04 Partial Complete
2026-02-05 Re add missing files
2026-02-05 refix ConfigCommandHandler
2026-02-06 Tone manager for control panel
2026-02-06 Share tonemanager
2026-02-07 Keep a couple of changes
2026-02-07 Initial sd card reader
2026-02-07 Minor fixes
2026-02-07 New Warning Type
2026-02-08 Minor tweaks
2026-02-08 Partially updated
2026-02-08 Fixed header after data loss
2026-02-08 card loader config
2026-02-08 Remove duplicate file
2026-02-08 Initial sd card config loader
2026-02-08 allow config load from sd card
2026-02-08 Finish SD integration
2026-02-08 Change from code review
2026-02-12 Integrate DS1302 RTC
2026-02-18 Integrate warnings
2026-02-18 updates after code review
2026-02-18 Feature/sd card driver (#111)
    * MicroSdDriver
    * Integrate warnings
2026-02-19 Initial offering
2026-02-21 extend sensor handling to include generic MQTT info
2026-02-21 System sensor handler
2026-02-22 convert strings to progmem and better build the payload
2026-02-22 Synchronize time from HA with following automation
    alias: Send Time to Arduino
    trigger:
    - platform: time_pattern
    minutes: "/1"
    action:
    - service: mqtt.publish
2026-02-23 Pre update changes
2026-02-23 Fix issue with relay controller
2026-02-26 Initial RemoteSensor
2026-02-26 Integrate Remote Sensors
2026-02-26 Document updates
2026-03-01 Improve compiler define usage
2026-03-04 Updates from code review comments
2026-03-04 Final changes after code review
2026-03-04 Ensure SD Card is not included when compiler flag not set
2026-03-05 Demo mode and sd card handling updates
2026-03-05 Updates from code review
2026-03-05 Demo mode and sd card handling updates (#122)
    * Demo mode and sd card handling updates
    * Updates from code review
2026-03-06 Updates for scheduled events
2026-03-08 Complete scheduled events
2026-03-08 Fix line endings and add copyright comments (#124)
2026-03-09 Validation checks and warning removal
2026-03-09 Fixes from code review
2026-03-11 Integrate light sensor analogue pin auto turn on light relay if dark
2026-03-11 Integrate light sensor analogue pin auto turn on light relay if dark (#126)
    * Integrate light sensor analogue pin auto turn on light relay if dark
    * Updates from code review
2026-03-11 Prep for KiCad, add Esp32.md and images (#127)
    Update .gitattributes to make life easier so as not to accidentally override .ino and Local.h
2026-03-12 Introduce BoardConfig.h to split Board capabilities away from Local.h
    Update documentation
2026-03-12 Fix incorrect paths in .gitattributes merge=ours rules
2026-03-16 Fix warnings and ensure compiles on esp32
2026-03-17 Configurable names for sensors
2026-03-17 Configurable names for sensors (#138)
2026-03-18 Enhance MQTT Support
2026-03-19 Enhance MQTT Support (#139)
    * Enhance MQTT Support
    * Fixes from code review plus add sensor mqtt update frequency
2026-03-20 Configure DHT22 sensors x 4
2026-03-21 Fix ble
2026-03-21 Fix ble (#142)
2026-03-21 Update/gitattributes (#145)
    * update .gitattributes
    * update local after fixing .gitattributes
2026-03-21 update local (#146)
2026-03-27 Re-factor how relay information is stored in EEPROM
    Does not change actual relay code yet but set's the ground work
2026-03-27 Re-factor how relay information is stored in EEPROM (#148)
    * Re-factor how relay information is stored in EEPROM
    Does not change actual relay code yet but set's the ground work
    * Updates from code review and update boatcontrolpanel
2026-03-28 Remove sub folders to own repositories
2026-03-28 Boat control panel is in it's own repo
2026-03-28 Remove symlink files as no longer required and move 3mf items to own repository
2026-03-28 Restructure code to individual repositories (#149)
    * Remove sub folders to own repositories
    * Replace sym link files with proper copies
    * Boat control panel is in it's own repo
    * shared files form part of the main projects
    * Remove symlink files as no longer required and move 3mf items to own repository
2026-03-29 Update relay commands,
2026-03-29 Update relay commands, (#150)
    This PR updates the relay/config command protocol to avoid command-prefix ambiguity and expands relay configuration capabilities (rename/color/default/link/actionType/pin), including persistence form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
2026-03-31 Dynamically create sensors based on Config (#154)
    * Dynamically create sensors based on Config
    * Fixes from code review
2026-03-31 Update required libraries
2026-03-31 Fix issue with card config loader and build in github
2026-03-31 .yml update
2026-03-31 update output path
2026-03-31 Add GitHub Actions workflow for firmware release
2026-04-02 Update GitHub Release action to use release directory
2026-04-02 fix(release): upload exactly 2x .bin and 2x .sha256 to GitHub Release for OTA
    Agent-Logs-Url: https://github.com/SmartFuseBox/SmartFuseBox/sessions/ec3f7729-d141-44ca-bab8-bd2692b948a5
2026-04-02 Fix formatting in release.yml
2026-04-02 Refactor GitHub Actions for ESP32 and ESP32-S3 builds
2026-04-02 OTA Updates based on tags created via git
2026-04-02 OTA Updates based on tags created via git (#159)
    * OTA Updates based on tags created via git
    * Fixes from code review
2026-04-05 Wifi Command Bridge
2026-04-06 Apply reviewer feedback: fix time source mixing, typos, doc comments, vcxproj filters, and strtoull
    Agent-Logs-Url: https://github.com/SmartFuseBox/SmartFuseBox/sessions/9cc3b3e7-916a-4845-b9af-fabadb1c3d42
2026-04-07 Set lat lon from home assistant so it can be used to find sunset/sunr… (#171)
    * Set lat lon from home assistant so it can be used to find sunset/sunrise times
    * Fixes from code review
2026-04-12 Add ability to test SFB (#174)
2026-04-12 Rename folder to src and move .sln to top level
2026-04-12 Fix binary artifact paths and remove IDE-generated __vm files
    Agent-Logs-Url: https://github.com/SmartFuseBox/SmartFuseBox/sessions/8103cdfc-2efb-4f70-b9d5-d6d01c2185db
2026-04-18 Include Nextion code, increase test coverage
2026-04-18 Update build/release libraries
2026-04-18 Update build/release libraries / code fixes
2026-04-18 Temp remove ThreeWire
2026-04-18 Include Nextion code, increase test coverage (#178)
    This PR expands SmartFuseBox firmware support for Nextion-based UI pages and new configuration surfaces (pins, RTC, external sensors), and extends the repository’s command-driven test datasets to cov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
2026-04-19 Convert nextion to message bus
2026-04-19 Convert nextion to message bus (#181)
    * Convert nextion to message bus
    * Updates from code review
2026-04-20 Minor fixes and updates
2026-04-20 fixes and updates from code review
2026-04-21 Minor fixes and updates (#182)
    * Minor fixes and updates
2026-04-25 Add initial home page to control/view relay statuses and view sensor data
2026-04-26 Add initial home page to control/view relay statuses and view sensor … (#183)
    * Add initial home page to control/view relay statuses and view sensor data
    * fixes from code review
2026-04-27 update docs
2026-04-28 update docs (#184)
2026-04-28 Initial rename/new structure
2026-04-28 Add files to sln
2026-04-28 update build and release files
2026-04-29 rename elements
2026-04-29 final elements after local build
2026-04-29 Rename and restructure
    * Initial rename/new structure
    * Add files to sln
    * update build and release files
    * rename elements
    * final elements after local build
2026-04-29 fix includes for release error
2026-04-29 Remove DHT11 as unused
2026-04-29 fix includes for release error
    * fix includes for release error
    * Remove DHT11 as unused
2026-04-29 PCBWay
2026-04-30 Update message/details
